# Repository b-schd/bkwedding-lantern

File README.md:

# Wedding Lantern Project

**********
### Requirements 
- [KiCad](https://www.kicad.org) >= v7.0
- [Code Composer Studio](https://www.ti.com/tool/CCSTUDIO) >= v10

### Contents
- pcb_lantern: kicad project, schematic, and layout files for building our custom PCB
- ccstudio_code: microcontroller firmware (main.c) and other code composer studio project files.

### Materials
- Bill of materials for PCB is included in KiCad folder
- 2xAAA holder with wires
- 2xAAA batteries
- [6in paper lantern](https://www.amazon.com/Novelty-Place-White-Paper-Lanterns/dp/B016PMP7H2/)
- [2.54mm multi-colored shunt jumpers](https://www.amazon.com/California-JOS-Standard-Connection-Raspberry/dp/B0BRK334XH/)

### License
Distributed under the [Apache-2.0 license](http://www.apache.org/licenses/) 

  **********

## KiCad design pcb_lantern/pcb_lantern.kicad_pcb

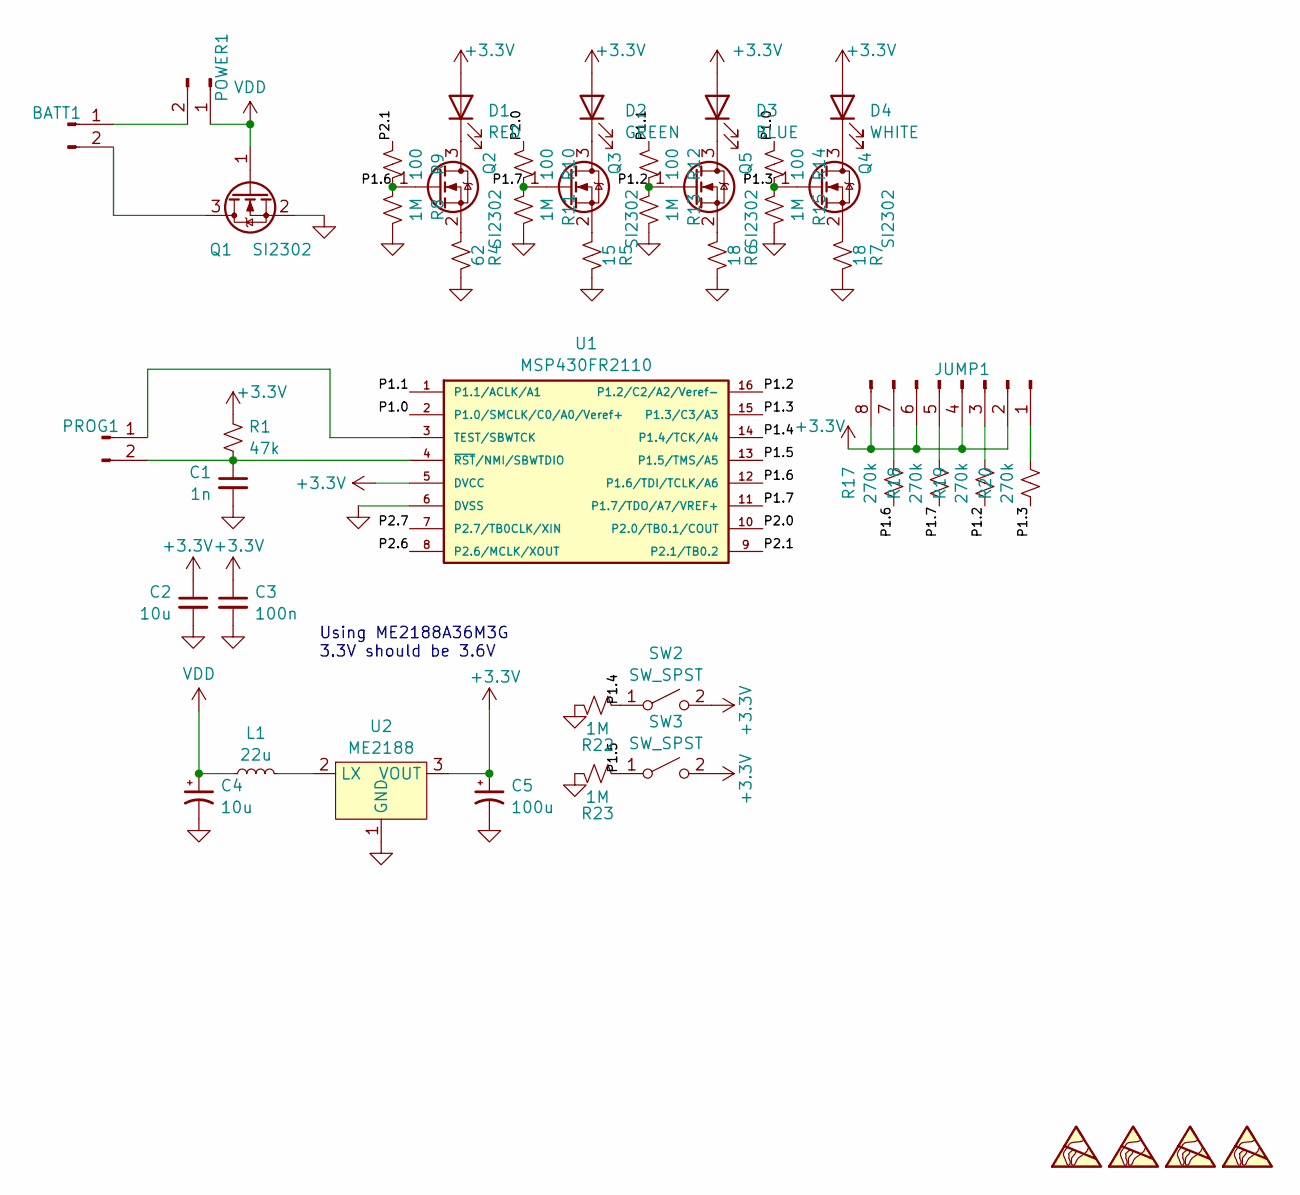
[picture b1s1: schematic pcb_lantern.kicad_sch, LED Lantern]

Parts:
BATT1: Conn_01x02_Pin; PinHeader_1x02_P2.54mm_Vertical; LCSC X
C1: 1n; C_0402_1005Metric; LCSC C106205
C2: 10u; C_0805_2012Metric_Pad1.18x1.45mm_HandSolder; LCSC C1713
C3: 100n; C_0603_1608Metric_Pad1.08x0.95mm_HandSolder; LCSC C30926
C4: 10u; CP_EIA-3216-18_Kemet-A; LCSC C185774
C5: 100u; CP_EIA-3528-21_Kemet-B; LCSC C140381
D1: RED; LED_PLCC_2835_Handsoldering; LCSC C5355467
D2: GREEN; LED_PLCC_2835_Handsoldering; LCSC C2843801
D3: BLUE; LED_PLCC_2835_Handsoldering; LCSC C2843802
D4: WHITE; LED_PLCC_2835_Handsoldering; LCSC C2843808
JUMP1: Conn_02x04_Pin; PinHeader_2x04_P2.54mm_Vertical_SMD; LCSC C2685176
L1: 22u; L_Taiyo-Yuden_NR-50xx; LCSC C440232
POWER1: Conn_01x02_Pin; PinHeader_1x02_P2.54mm_Vertical_SMD_Pin1Left; LCSC C5160785
PROG1: Conn_01x02_Pin; PinHeader_1x02_P2.54mm_Vertical; LCSC X
Q1, Q2, Q3, Q4, Q5: SI2302; SOT-23; LCSC C4748714
R1: 47k; R_0402_1005Metric; LCSC C25792
R4: 62; R_0805_2012Metric; LCSC C560547
R5: 15; R_0603_1608Metric; LCSC C966198
R6, R7: 18; R_0603_1608Metric; LCSC C966193
R8, R11, R13, R15, R22, R23: 1M; R_0402_1005Metric; LCSC C26083
R9, R10, R12, R14: 100; R_0402_1005Metric; LCSC C106232
R17, R18, R19, R20: 270k; R_0402_1005Metric; LCSC C2759500
SW2, SW3: SW_SPST; SW_Push_1P1T_XKB_TS-1187A; LCSC C318884
SYM1, SYM2, SYM3, SYM4: SYM_ESD_Small; MountingHole_2.5mm; LCSC X
U1: MSP430FR2110; TSSOP-16_4.4x5mm_P0.65mm; LCSC C174367
U2: ME2188; SOT-23; LCSC C236773

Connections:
+3.3V: C2.1, C3.1, C5.1, D1.2 (A), D2.2 (A), D3.2 (A), D4.2 (A), JUMP1.2, JUMP1.4, JUMP1.6, JUMP1.8, R1.1, SW2.2 (B), SW3.2 (B), U1.5 (DVCC), U2.3 (VOUT)
/P1.0: R14.2, U1.2 (P1.0/SMCLK/C0/A0/Veref+)
/P1.1: R12.2, U1.1 (P1.1/ACLK/A1)
/P1.2: Q5.1 (G), R12.1, R13.2, R19.1, U1.16 (P1.2/C2/A2/Veref-)
/P1.3: Q4.1 (G), R14.1, R15.2, R20.1, U1.15 (P1.3/C3/A3)
/P1.4: R22.2, SW2.1 (A), U1.14 (P1.4/TCK/A4)
/P1.5: R23.2, SW3.1 (A), U1.13 (P1.5/TMS/A5)
/P1.6: Q2.1 (G), R8.2, R9.1, R17.1, U1.12 (P1.6/TDI/TCLK/A6)
/P1.7: Q3.1 (G), R10.1, R11.2, R18.1, U1.11 (P1.7/TDO/A7/VREF+)
/P2.0: R10.2, U1.10 (P2.0/TB0.1/COUT)
/P2.1: R9.2, U1.9 (P2.1/TB0.2)
/P2.6: U1.8 (P2.6/MCLK/XOUT)
/P2.7: U1.7 (P2.7/TB0CLK/XIN)
GND: C1.2, C2.2, C3.2, C4.2, C5.2, Q1.2 (S), R4.1, R5.1, R6.1, R7.1, R8.1, R11.1, R13.1, R15.1, R22.1, R23.1, U1.6 (DVSS), U2.1 (GND)
unnamed: BATT1.1, POWER1.2
unnamed: BATT1.2, Q1.3 (D)
unnamed: D1.1 (K), Q2.3 (D)
unnamed: D2.1 (K), Q3.3 (D)
unnamed: D3.1 (K), Q5.3 (D)
unnamed: D4.1 (K), Q4.3 (D)
unnamed: JUMP1.1, R20.2
unnamed: JUMP1.3, R19.2
unnamed: JUMP1.5, R18.2
unnamed: JUMP1.7, R17.2
unnamed: PROG1.1, U1.3 (TEST/SBWTCK)
unnamed: C1.1, PROG1.2, R1.2, U1.4 (~RST/NMI/SBWTDIO)
unnamed: Q2.2 (S), R4.2
unnamed: Q3.2 (S), R5.2
unnamed: Q4.2 (S), R7.2
unnamed: Q5.2 (S), R6.2
unnamed: L1.2, U2.2 (LX)
VDD: C4.1, L1.1, POWER1.1, Q1.1 (G)

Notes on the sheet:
Using ME2188A36M3G 3.3V should be 3.6V

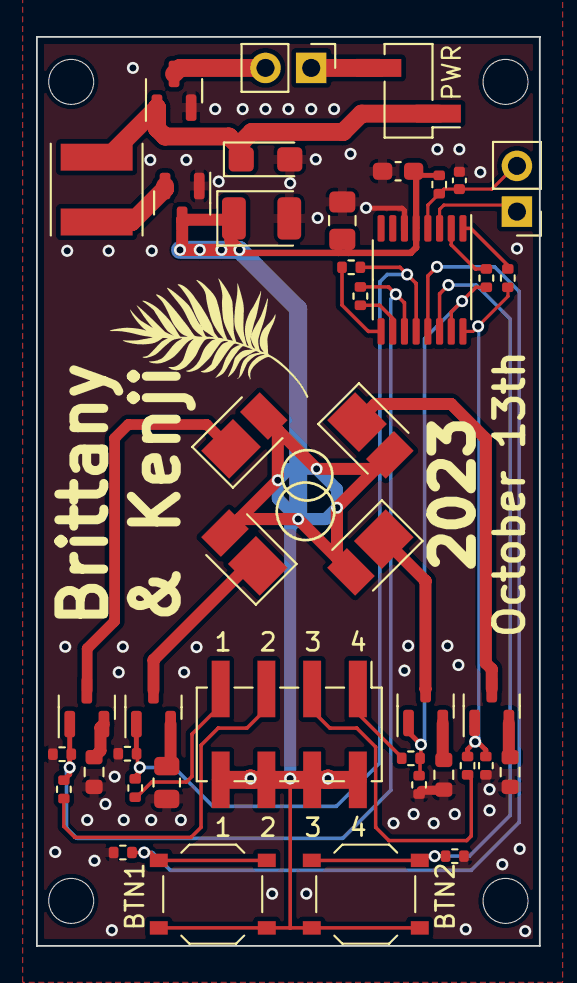
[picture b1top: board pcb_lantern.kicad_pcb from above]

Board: 2 copper layers, 27.9 x 50.5 mm, 46 parts (0 on the bottom side), 30 nets.

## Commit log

2023-10-21 lantern pcb files
    lantern files
